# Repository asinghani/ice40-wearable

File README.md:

# iCE40 Wearables

This repo contains board designs (KiCad) for two iCE40 FPGA-based boards: one in a sewable form-factor and one in a cat-ear form factor.

### Board 1: Sewable

This board is inspired by the [Adafruit Flora](https://www.adafruit.com/product/659) and is meant to be sewn into clothing or accessories. It is shaped as a small circle and has all the components on the front side to allow it to sit flush against a flat surface. It includes the following features:

- iCE40UP5K FPGA
- 16Mb QSPI Flash (GD25Q16CSIGR)
- 16MHz Oscillator (SIT2001BI, multiple frequency options available)
- PWR/DONE/USER LEDs, USER pushbutton
- RGB LED (WS2812)
- 14 Electric Sewing Pads: 12x GPIO, 1x 3V3, 1x GND
- USB-C port
- JST power header
- Tag-Connect programming header

Schematic is in [ice40_sewable_board/schematic.pdf](ice40_sewable_board/schematic.pdf)

An example design (that utilizes the button, USER LED, RGB LED, and one of the sewing pads) is in [ice40_sewable_ref_design/](ice40_sewable_ref_design/)

### Board 2: Cat-ears

This board is meant to be shaped like a cat-ear, such that two of them can be worn on a headband (the GPIO pins can be wired together to provide synchronization between the ears). It was designed as a tribute to [YosysHQ](https://www.yosyshq.com/) who develop open-source FPGA software tooling. Each ear includes the following features:

- iCE40UP5K FPGA (internal 48MHz oscillator is used to simplify BOM)
- 16Mb QSPI Flash (GD25Q16CSIGR)
- 7x RGB LED (WS2812)
- Power options: JST power header OR CR2032 coin cell holder
- 2.54mm programming & GPIO header (can be programmed with small wire clips or by soldering)
- Additional GPIO pads on rear side for soldering

Schematic is in [ice40_catears_board/schematic.pdf](ice40_catears_board/schematic.pdf)

An example design (that builds separate modules for the left and right ears, and utilizes the RGB LEDs and GPIO pads) is in [ice40_catears_ref_design/](ice40_catears_ref_design/)

### Acknowledgements

Board design was inspired by [electronutlabs-public/ice-bling](https://gitlab.com/electronutlabs-public/ice-bling) and [icebreaker-fpga/icebreaker](https://github.com/icebreaker-fpga/icebreaker). CMU TechSpark and RoboClub were used for fabrication and materials.

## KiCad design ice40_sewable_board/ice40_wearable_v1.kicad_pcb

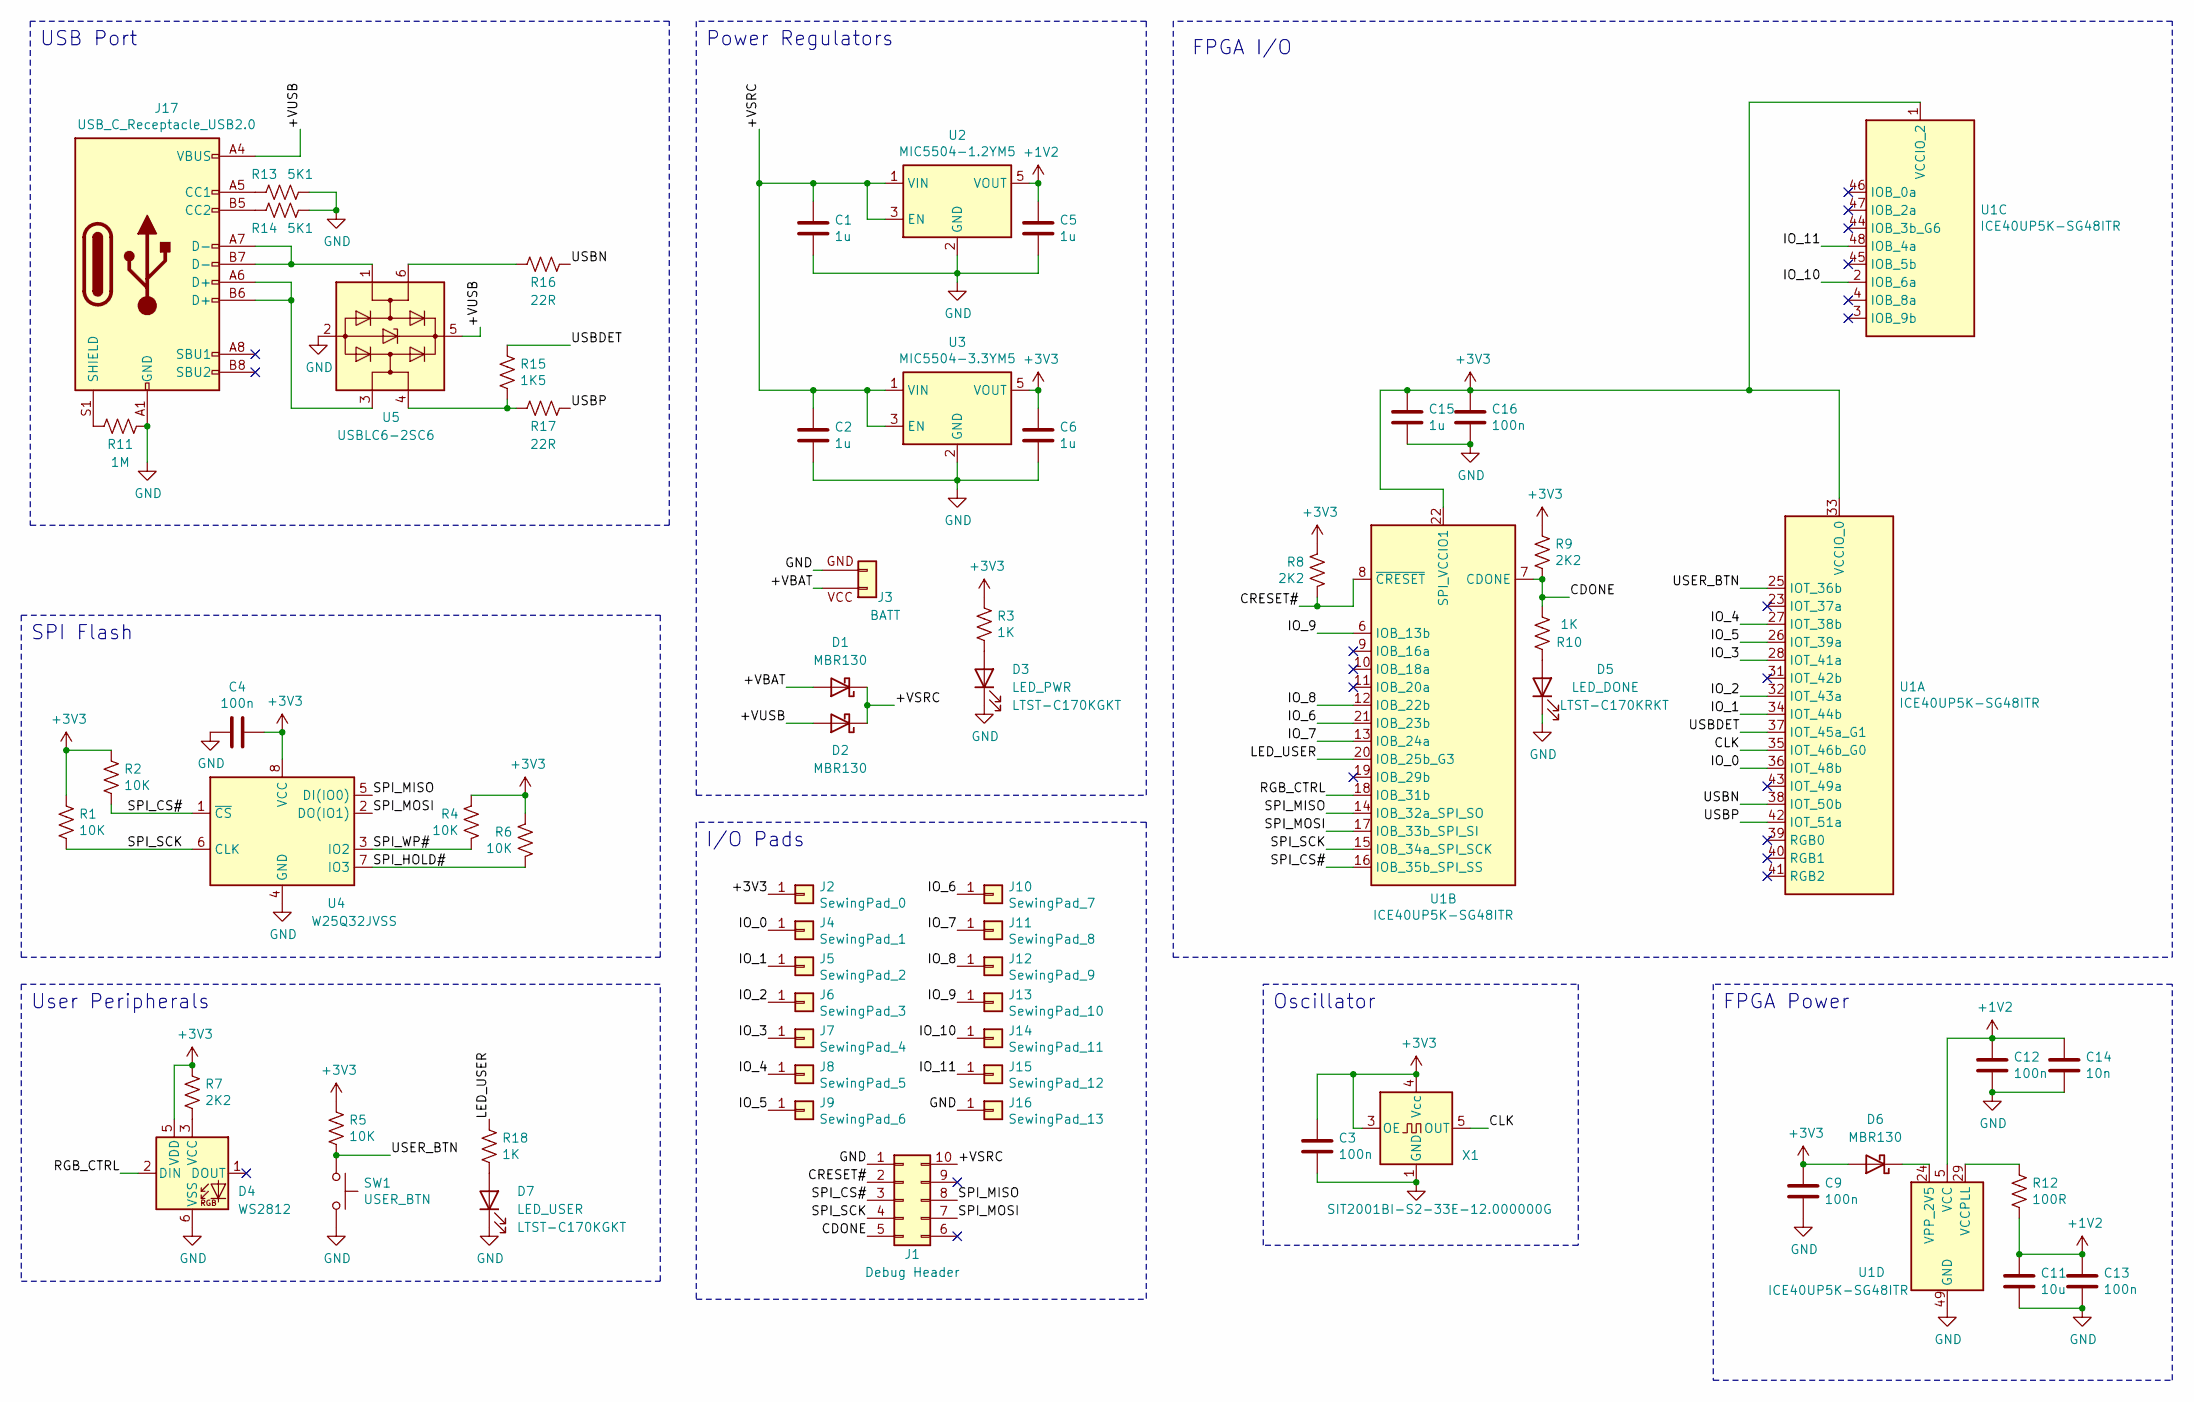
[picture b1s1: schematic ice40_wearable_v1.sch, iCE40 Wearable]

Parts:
C1, C2, C5, C6, C15: 1u; C_0603_1608Metric
C3, C4, C9, C12, C13, C16: 100n; C_0603_1608Metric
C11: 10u; C_0603_1608Metric
C14: 10n; C_0603_1608Metric
D1, D2, D6: MBR130; D_SOD-123
D3: LED_PWR; LED_0805_2012Metric
D4: WS2812; LED_WS2812_PLCC6_5.0x5.0mm_P1.6mm
D5: LED_DONE; LED_0805_2012Metric
D7: LED_USER; LED_0805_2012Metric
J1: Debug Header; Tag-Connect_TC2050-IDC-NL_2x05_P1.27mm_Vertical_with_bottom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
J2: SewingPad_0; adafruit_sewing_tap
J3: BATT; JST_PH_S2B-PH-SM4-TB_1x02-1MP_P2.00mm_Horizontal
J4: SewingPad_1; adafruit_sewing_tap
J5: SewingPad_2; adafruit_sewing_tap
J6: SewingPad_3; adafruit_sewing_tap
J7: SewingPad_4; adafruit_sewing_tap
J8: SewingPad_5; adafruit_sewing_tap
J9: SewingPad_6; adafruit_sewing_tap
J10: SewingPad_7; adafruit_sewing_tap
J11: SewingPad_8; adafruit_sewing_tap
J12: SewingPad_9; adafruit_sewing_tap
J13: SewingPad_10; adafruit_sewing_tap
J14: SewingPad_11; adafruit_sewing_tap
J15: SewingPad_12; adafruit_sewing_tap
J16: SewingPad_13; adafruit_sewing_tap
J17: USB_C_Receptacle_USB2.0; USB_C_Receptacle_HRO_TYPE-C-31-M-12
R1, R2, R4, R5, R6: 10K; R_0805_2012Metric
R3, R10, R18: 1K; R_0805_2012Metric
R7, R8, R9: 2K2; R_0805_2012Metric
R11: 1M; R_0805_2012Metric
R12: 100R; R_0805_2012Metric
R13, R14: 5K1; R_0805_2012Metric
R15: 1K5; R_0805_2012Metric
R16, R17: 22R; R_0805_2012Metric
SW1: USER_BTN; SW_SPST_CK_RS282G05A3
U1: ICE40UP5K-SG48ITR; QFN-48-1EP_7x7mm_P0.5mm_EP5.6x5.6mm
U2: MIC5504-1.2YM5; SOT-23-5
U3: MIC5504-3.3YM5; SOT-23-5
U4: W25Q32JVSS; SOIC-8_5.23x5.23mm_P1.27mm
U5: USBLC6-2SC6; SOT-23-6
X1: SIT2001BI-S2-33E-12.000000G; SOT-23-5

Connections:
+1V2: C5.1, C11.1, C12.1, C13.1, C14.1, R12.2, U1.5 (VCC), U1.30 (VCC), U2.5 (VOUT)
+3V3: C3.1, C4.1, C6.1, C9.1, C15.1, C16.1, D4.5 (VDD), D6.2 (A), J2.1, R1.1, R2.1, R3.1, R4.2, R5.1, R6.1, R7.1, R8.1, R9.1, U1.1 (VCCIO_2), U1.22 (SPI_VCCIO1), U1.33 (VCCIO_0), U3.5 (VOUT), U4.8 (VCC), X1.3 (OE), X1.4 (Vcc)
/+VBAT: D1.2 (A), J3.1 (+V)
/+VSRC: C1.1, C2.1, D1.1 (K), D2.1 (K), J1.10, U2.1 (VIN), U2.3 (EN), U3.1 (VIN), U3.3 (EN)
/+VUSB: D2.2 (A), J17.A4 (VBUS), J17.A9 (VBUS), J17.B4 (VBUS), J17.B9 (VBUS), U5.5 (VBUS)
/CDONE: J1.5, R9.2, R10.2, U1.7 (CDONE)
/CLK: U1.35 (IOT_46b_G0), X1.5 (OUT)
/CRESET#: J1.2, R8.2, U1.8 (~CRESET)
/IO_0: J4.1, U1.36 (IOT_48b)
/IO_1: J5.1, U1.34 (IOT_44b)
/IO_2: J6.1, U1.32 (IOT_43a)
/IO_3: J7.1, U1.28 (IOT_41a)
/IO_4: J8.1, U1.27 (IOT_38b)
/IO_5: J9.1, U1.26 (IOT_39a)
/IO_6: J10.1, U1.21 (IOB_23b)
/IO_7: J11.1, U1.13 (IOB_24a)
/IO_8: J12.1, U1.12 (IOB_22b)
/IO_9: J13.1, U1.6 (IOB_13b)
/IO_10: J14.1, U1.2 (IOB_6a)
/IO_11: J15.1, U1.48 (IOB_4a)
/LED_USER: R18.1, U1.20 (IOB_25b_G3)
/RGB_CTRL: D4.2 (DIN), U1.18 (IOB_31b)
/SPI_CS#: J1.3, R2.2, U1.16 (IOB_35b_SPI_SS), U4.1 (~CS)
/SPI_HOLD#: R6.2, U4.7 (IO3)
/SPI_MISO: J1.8, U1.14 (IOB_32a_SPI_SO), U4.5 (DI(IO0))
/SPI_MOSI: J1.7, U1.17 (IOB_33b_SPI_SI), U4.2 (DO(IO1))
/SPI_SCK: J1.4, R1.2, U1.15 (IOB_34a_SPI_SCK), U4.6 (CLK)
/SPI_WP#: R4.1, U4.3 (IO2)
/USBDET: R15.1, U1.37 (IOT_45a_G1)
/USBN: R16.2, U1.38 (IOT_50b)
/USBP: R17.2, U1.42 (IOT_51a)
/USER_BTN: R5.2, SW1.1, U1.25 (IOT_36b)
GND: C1.2, C2.2, C3.2, C4.2, C5.2, C6.2, C9.2, C11.2, C12.2, C13.2, C14.2, C15.2, C16.2, D3.1 (K), D4.6 (VSS), D5.1 (K), D7.1 (K), J1.1, J3.2 (GND), J16.1, J17.A1 (GND), J17.A12 (GND), J17.B1 (GND), J17.B12 (GND), R11.2, R13.2, R14.2, SW1.2, U1.49 (GND), U2.2 (GND), U3.2 (GND), U4.4 (GND), U5.2 (GND), X1.1 (GND)
unnamed: D3.2 (A), R3.2
unnamed: D4.3 (VCC), R7.2
unnamed: D5.2 (A), R10.1
unnamed: D6.1 (K), U1.24 (VPP_2V5)
unnamed: D7.2 (A), R18.2
unnamed: J17.A5 (CC1), R13.1
unnamed: J17.A6 (D+), J17.B6 (D+), U5.3 (I/O2)
unnamed: J17.A7 (D-), J17.B7 (D-), U5.1 (I/O1)
unnamed: J17.B5 (CC2), R14.1
unnamed: J17.S1 (SHIELD), R11.1
unnamed: R12.1, U1.29 (VCCPLL)
unnamed: R15.2, R17.1, U5.4 (I/O2)
unnamed: R16.1, U5.6 (I/O1)

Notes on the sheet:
User Peripherals
SPI Flash
Power Regulators
USB Port
FPGA Power
FPGA I/O
I/O Pads
Oscillator

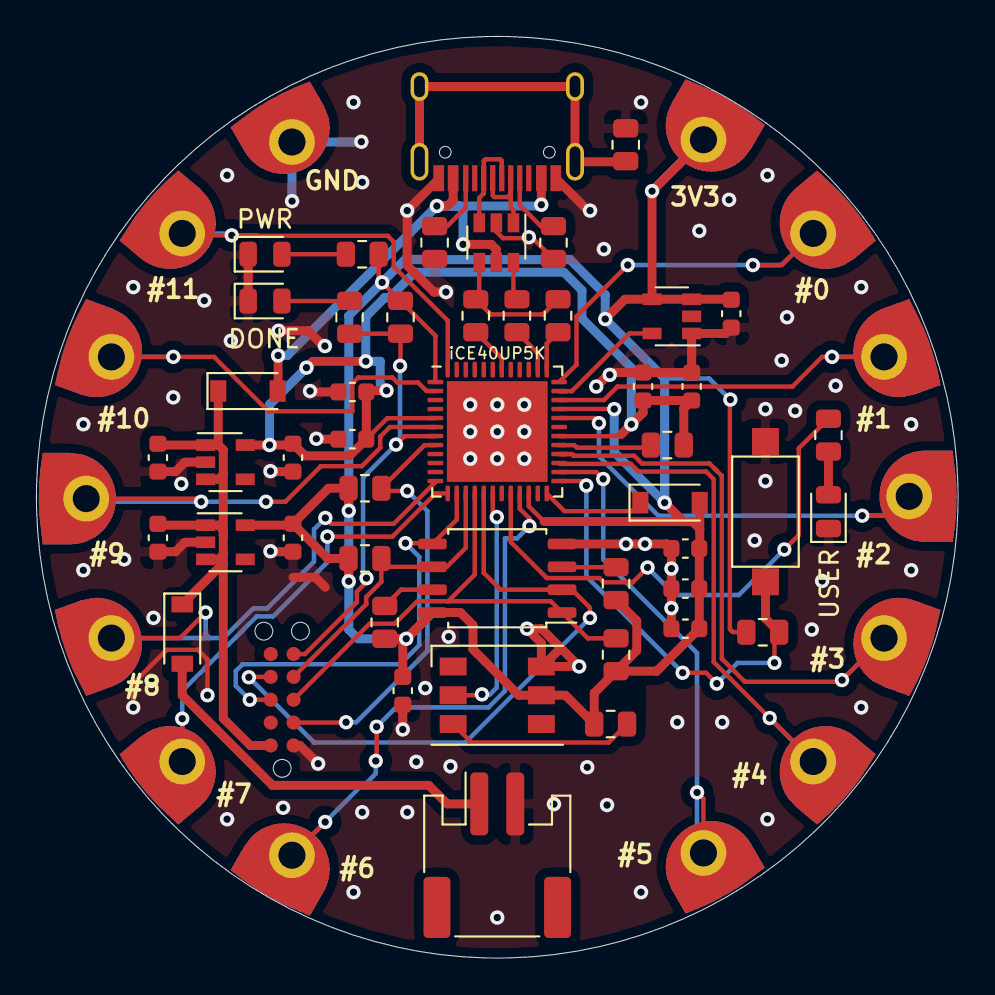
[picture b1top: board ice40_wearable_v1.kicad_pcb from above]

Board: 2 copper layers, 51.2 x 51.2 mm, 62 parts (0 on the bottom side), 46 nets.

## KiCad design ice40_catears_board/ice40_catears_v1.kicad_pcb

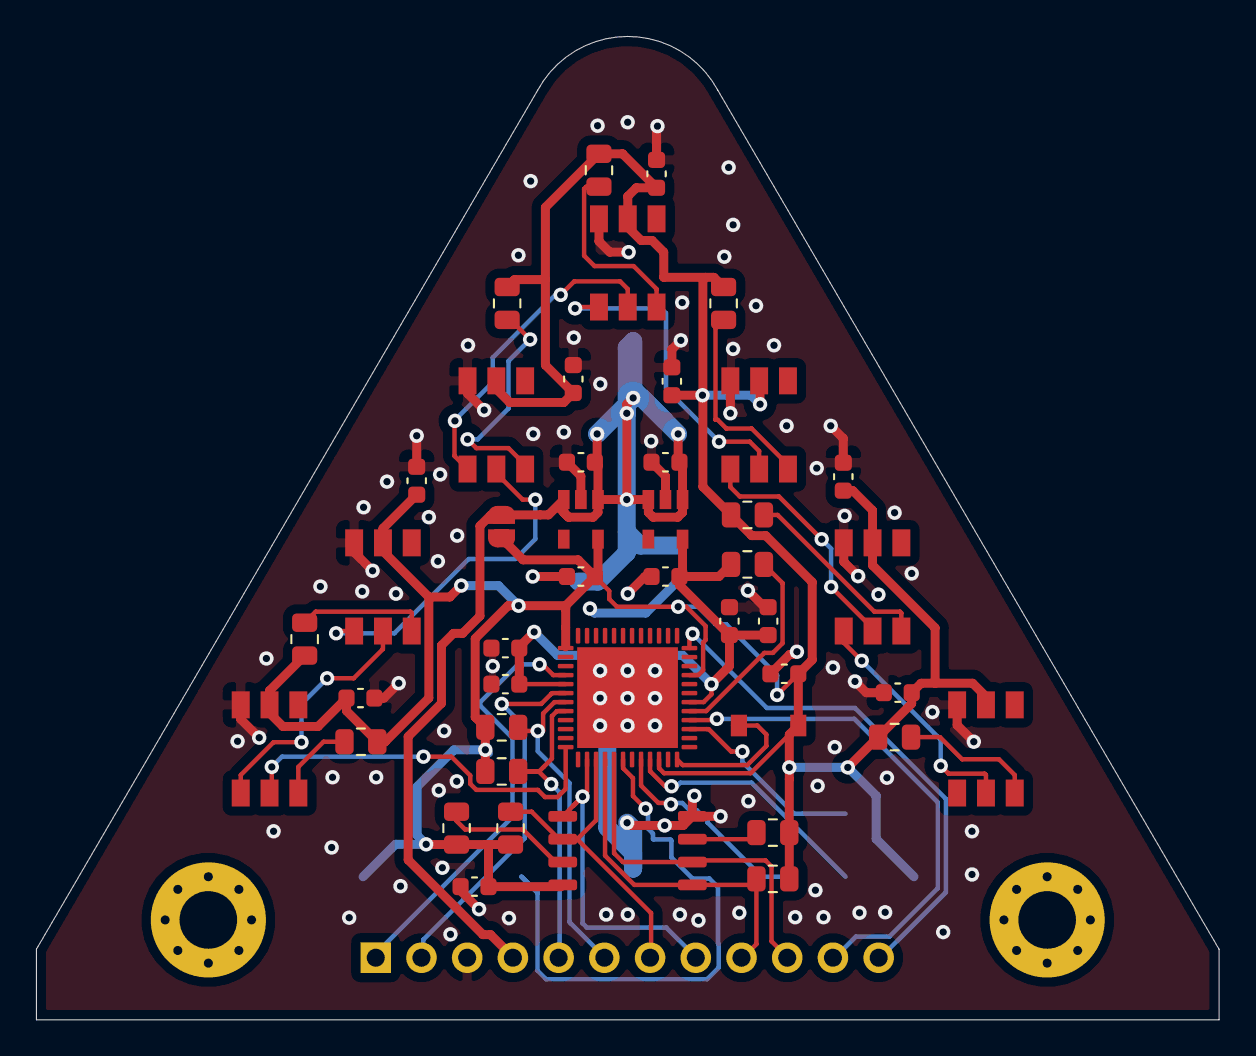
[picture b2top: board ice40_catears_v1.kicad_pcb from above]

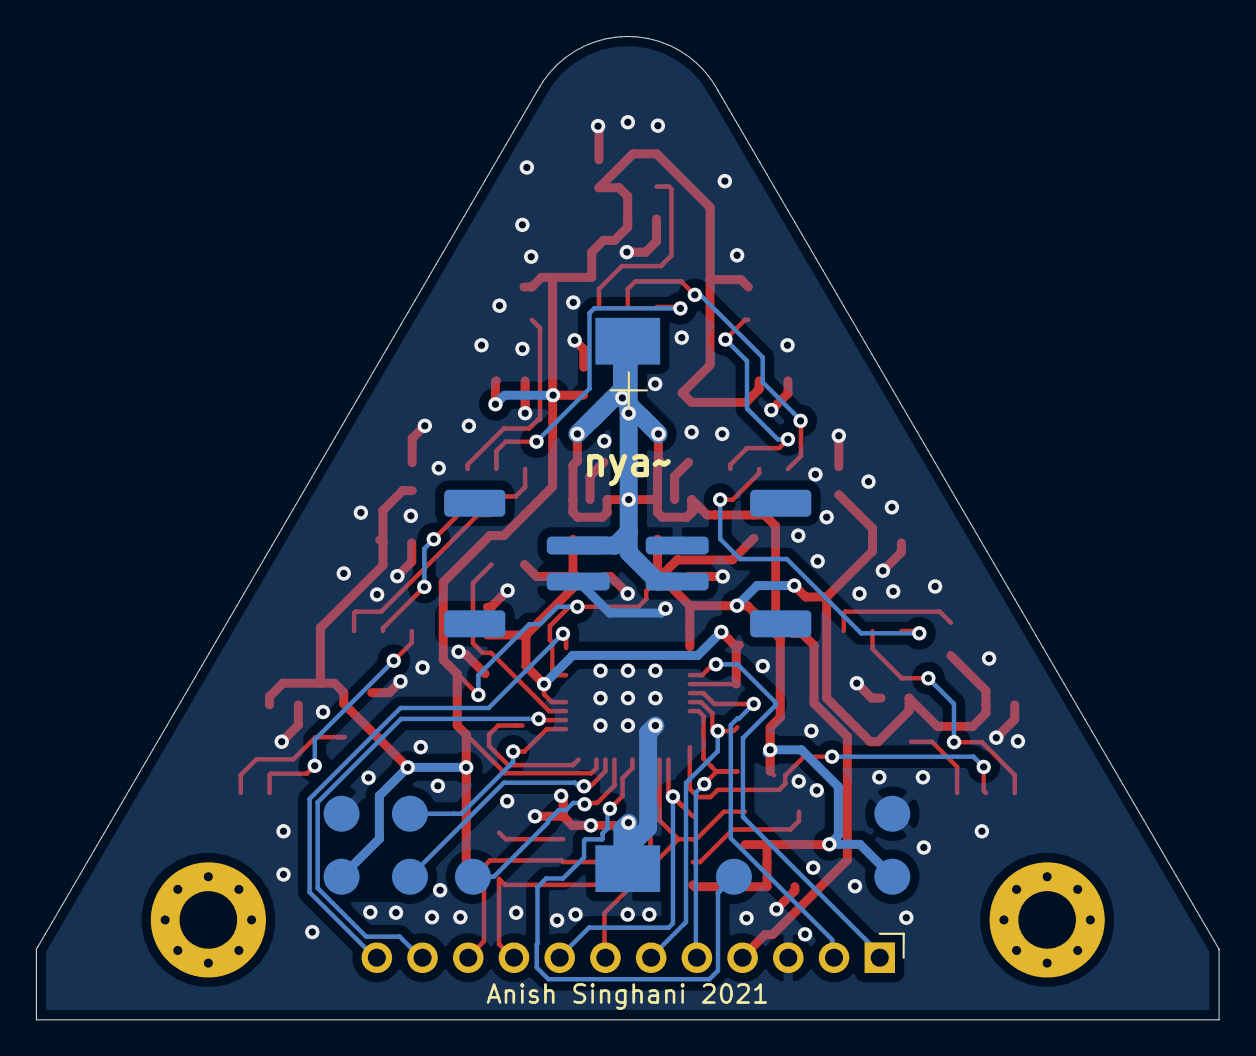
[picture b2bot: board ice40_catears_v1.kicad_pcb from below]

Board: 2 copper layers, 65.7 x 54.6 mm, 58 parts (12 on the bottom side), 36 nets.

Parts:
BT1: CR2032; BatteryHolder_Keystone_1060_1x2032
C1, C2, C7, C8, C9, C11, C13, C14, C15, C16, C17: 100n; C_0603_1608Metric
C3, C4, C5, C6: 1u; C_0603_1608Metric
C10: 10u; C_0603_1608Metric
C12: 10n; C_0603_1608Metric
D1: WS2812-TOP; LED_WS2812_PLCC6_5.0x5.0mm_P1.6mm
D2: WS2812-L2; LED_WS2812_PLCC6_5.0x5.0mm_P1.6mm
D3: MBR130; D_SOD-123
D4: WS2812-R2; LED_WS2812_PLCC6_5.0x5.0mm_P1.6mm
D5: WS2812-R1; LED_WS2812_PLCC6_5.0x5.0mm_P1.6mm
D6: WS2812-L1; LED_WS2812_PLCC6_5.0x5.0mm_P1.6mm
D7: WS2812-R3; LED_WS2812_PLCC6_5.0x5.0mm_P1.6mm
D8: WS2812-L3; LED_WS2812_PLCC6_5.0x5.0mm_P1.6mm
H1: MountingHole-L; MountingHole_3.2mm_M3_Pad_Via
H2: MountingHole-R; MountingHole_3.2mm_M3_Pad_Via
J1: BATT-R; JST_PH_S2B-PH-SM4-TB_1x02-1MP_P2.00mm_Horizontal
J2: BATT-L; JST_PH_S2B-PH-SM4-TB_1x02-1MP_P2.00mm_Horizontal
J3: Debug Header; PinHeader_1x12_P2.54mm_Vertical
JP1: 3.3-BYPASS; SolderJumper-2_P1.3mm_Open_RoundedPad1.0x1.5mm
R1, R2, R7, R9, R10, R11, R12, R13, R14: 2K2; R_0805_2012Metric
R3, R4, R5, R6: 10K; R_0805_2012Metric
R8: 100R; R_0805_2012Metric
TP1, TP4: TP_3V3; TestPoint_Pad_D2.0mm
TP2, TP5: TP_GND; TestPoint_Pad_D2.0mm
TP3, TP7, TP10, TP11: TP; TestPoint_Pad_D2.0mm
U1: W25Q32JVSS; SOIC-8_5.23x5.23mm_P1.27mm
U2: MIC5504-1.2YM5; SOT-23-5
U3: MIC5504-3.3YM5; SOT-23-5
U4: ICE40UP5K-SG48ITR; QFN-48-1EP_7x7mm_P0.5mm_EP5.6x5.6mm

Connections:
+1V2: C5.1, C9.1, C10.1, C12.1, C13.1, R8.2, U2.5, U4.5, U4.30
+3V3: C1.2, C2.1, C6.1, C7.1, C8.2, C11.2, C14.2, C15.2, C16.2, C17.2, D1.5, D2.5, D3.2, D4.5, D5.5, D6.5, D7.5, D8.5, JP1.2, R1.1, R2.1, R3.1, R4.1, R5.2, R6.1, R7.1, R9.1, R10.1, R11.1, R12.1, R13.1, R14.1, TP1.1, TP4.1, U1.8, U3.5, U4.1, U4.22, U4.33
/+VSRC: BT1.1, C3.1, C4.1, J1.1, J2.1, J3.4, JP1.1, U2.1, U2.3, U3.1, U3.3
/CDONE: J3.6, R9.2, U4.7
/CRESET#: J3.5, R7.2, U4.8
/GPIO_1: TP3.1, U4.18
/GPIO_2: TP7.1, U4.20
/GPIO_3: TP10.1, U4.21
/GPIO_4: TP11.1, U4.27
/GPIO_5: J3.1, U4.4
/GPIO_6: J3.2, U4.6
/GPIO_7: J3.11, U4.28
/GPIO_8: J3.12, U4.36
/RGB_CTRL: D8.2, U4.12
/SPI_CS#: J3.9, R4.2, U1.1, U4.16
/SPI_HOLD#: R6.2, U1.7
/SPI_MISO: J3.8, U1.5, U4.14
/SPI_MOSI: J3.10, U1.2, U4.17
/SPI_SCK: J3.7, R3.2, U1.6, U4.15
/SPI_WP#: R5.1, U1.3
GND: BT1.2, C1.1, C2.2, C3.2, C4.2, C5.2, C6.2, C7.2, C8.1, C9.2, C10.2, C11.1, C12.2, C13.2, C14.1, C15.1, C16.1, C17.1, D1.6, D2.6, D4.6, D5.6, D6.6, D7.6, D8.6, J1.2, J2.2, J3.3, TP2.1, TP5.1, U1.4, U2.2, U3.2, U4.49
unnamed: D1.1, D5.2
unnamed: D1.2, D6.1
unnamed: D1.3, R1.2
unnamed: D2.1, D6.2
unnamed: D2.2, D8.1
unnamed: D2.3, R2.2
unnamed: D3.1, U4.24
unnamed: D4.1, D7.2
unnamed: D4.2, D5.1
unnamed: D4.3, R10.2
unnamed: D5.3, R11.2
unnamed: D6.3, R12.2
unnamed: D7.3, R13.2
unnamed: D8.3, R14.2
unnamed: R8.1, U4.29

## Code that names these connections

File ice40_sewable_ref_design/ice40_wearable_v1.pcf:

########################################################################
# Main constraints file for iCE40 wearable board
########################################################################

# Main clock (16 MHz)
set_io clk 35

# Direct USB
set_io usbp   42
set_io usbn   38
set_io usbdet 37

# SPI Flash
set_io flash_csn 16 # SPI_CS# on schem
set_io flash_sck 15 # SPI_SCK on schem
set_io flash_io0 14 # SPI_MISO on schem
set_io flash_io1 17 # SPI_MOSI on schem

# Sewing Pad I/O Ports
set_io io_0  36
set_io io_1  34
set_io io_2  32
set_io io_3  28
set_io io_4  27
set_io io_5  26
set_io io_6  21
set_io io_7  13
set_io io_8  12
set_io io_9  6
set_io io_10 2
set_io io_11 48

# On-board Peripherals
set_io led_user   20
set_io btn_user_n 25
set_io rgb_led    18

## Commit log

2021-12-23 Add designs
